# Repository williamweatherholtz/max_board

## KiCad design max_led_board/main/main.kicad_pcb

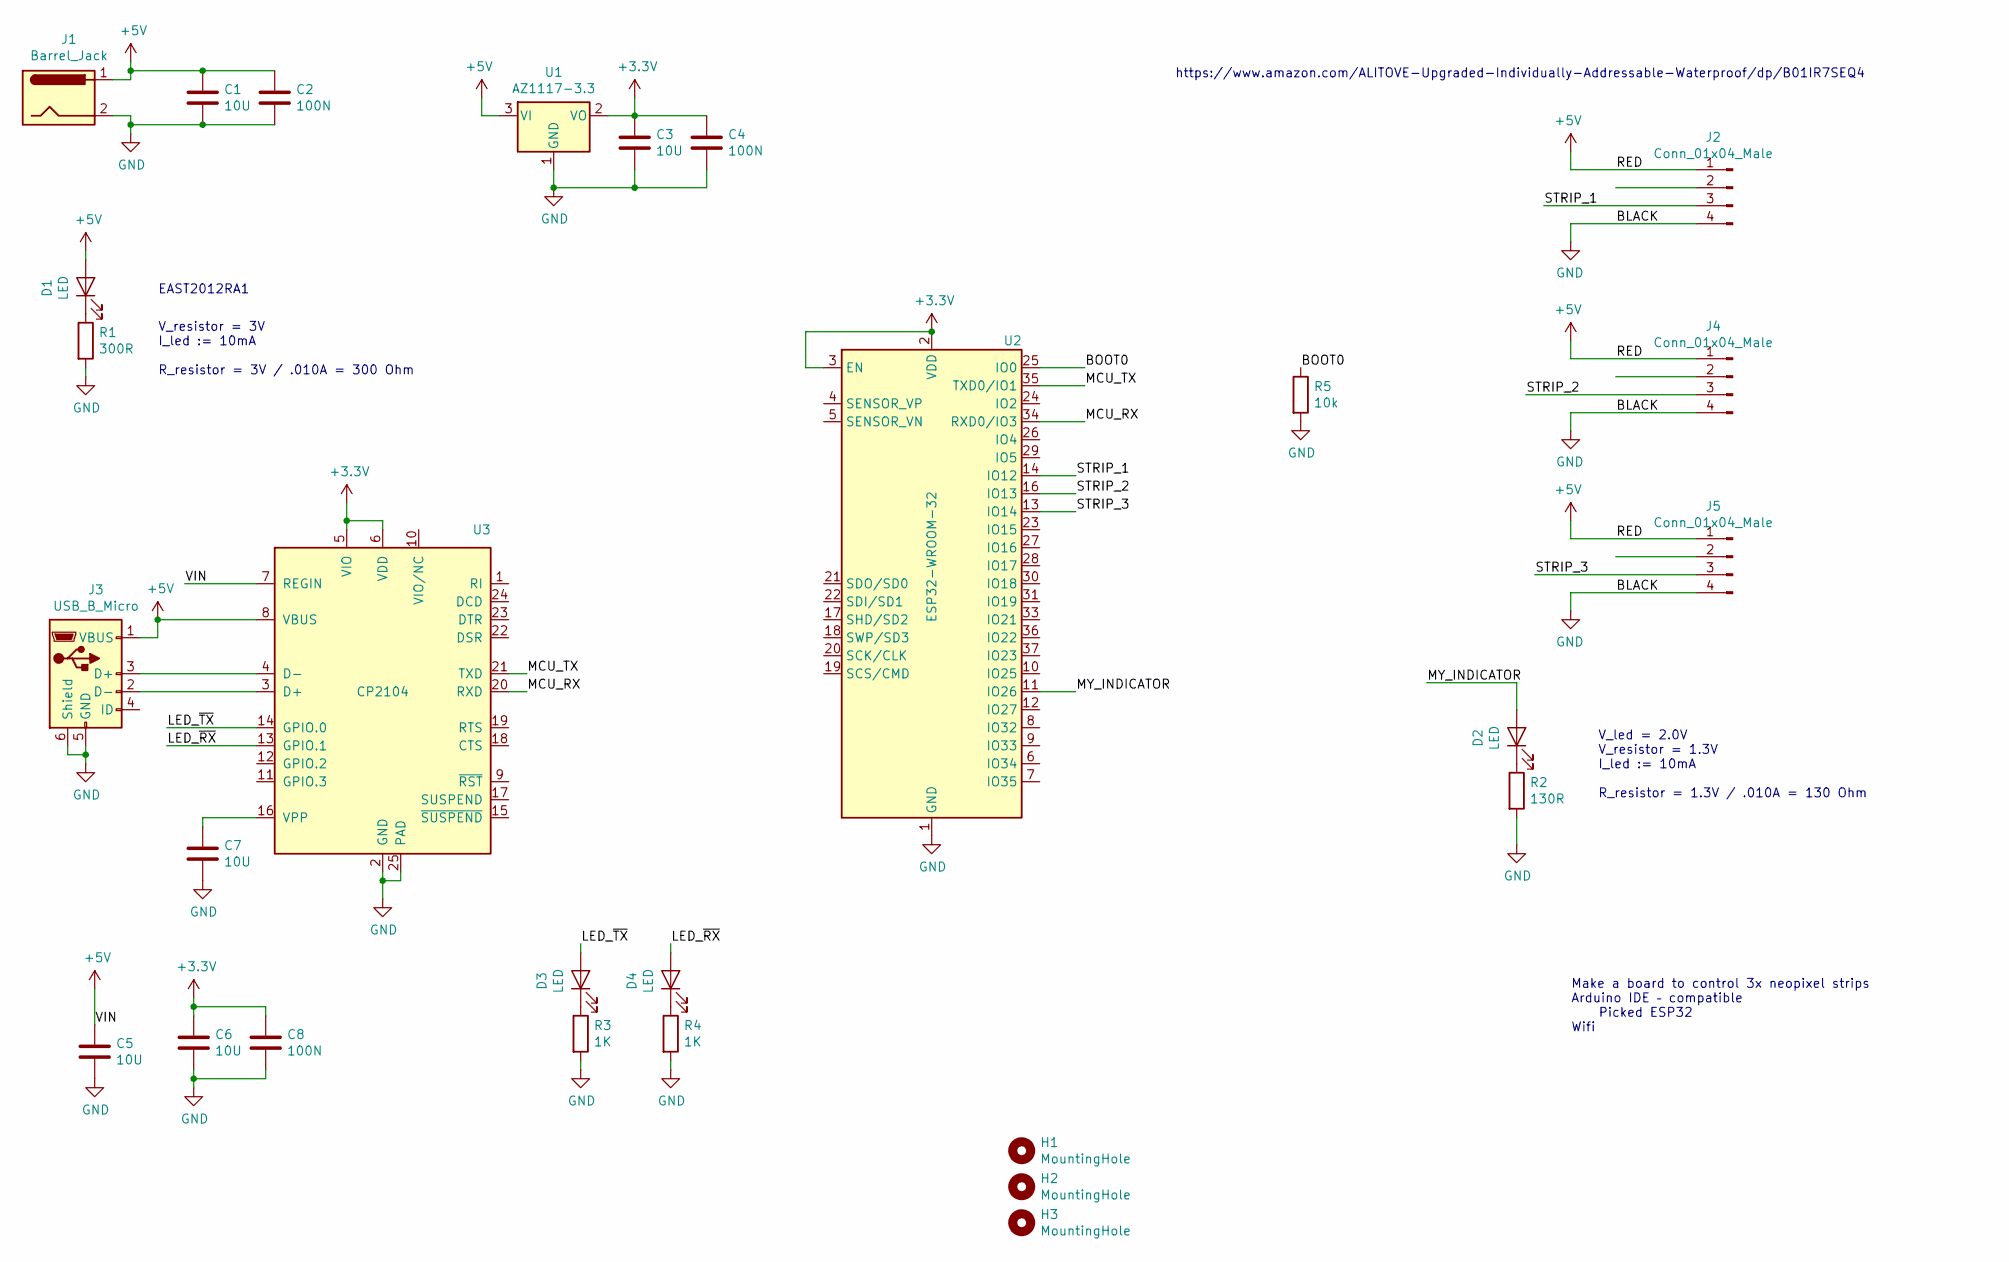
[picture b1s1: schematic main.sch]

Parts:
C1, C3, C5, C6, C7: 10U; C_0805_2012Metric
C2, C4, C8: 100N; C_0603_1608Metric
D1, D2, D3, D4: LED; LED_0805_2012Metric
H1, H2, H3: MountingHole; MountingHole_4.3mm_M4
J1: Barrel_Jack; BarrelJack_Wuerth_6941xx301002
J2, J4, J5: Conn_01x04_Male; PinHeader_1x04_P2.54mm_Vertical
J3: USB_B_Micro; USB_Micro_B_Female_10118194-0001LF
R1: 300R; R_0603_1608Metric
R2: 130R; R_0603_1608Metric
R3, R4: 1K; R_0603_1608Metric
R5: 10k; R_0603_1608Metric
U1: AZ1117-3.3; SOT-223-3_TabPin2
U2: ESP32-WROOM-32
U3: CP2104; QFN-24-1EP_4x4mm_P0.5mm_EP2.6x2.6mm

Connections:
+3V3: C3.1, C4.1, C6.1, C8.1, U1.2 (VO), U2.2 (VDD), U2.3 (EN), U3.5 (VIO), U3.6 (VDD)
+5V: C1.1, C2.1, C5.1, D1.2 (A), J1.1, J2.1, J3.1 (VBUS), J4.1, J5.1, U1.3 (VI), U3.7 (REGIN), U3.8 (VBUS)
/BOOT0: R5.1, U2.25 (IO0)
/LED_~RX~: D4.2 (A), U3.13 (GPIO.1)
/LED_~TX~: D3.2 (A), U3.14 (GPIO.0)
/MCU_RX: U2.34 (RXD0/IO3), U3.20 (RXD)
/MCU_TX: U2.35 (TXD0/IO1), U3.21 (TXD)
/MY_INDICATOR: D2.2 (A), U2.11 (IO26)
/STRIP_1: J2.3, U2.14 (IO12)
/STRIP_2: J4.3, U2.16 (IO13)
/STRIP_3: J5.3, U2.13 (IO14)
GND: C1.2, C2.2, C3.2, C4.2, C5.2, C6.2, C7.2, C8.2, J1.2, J2.4, J3.5 (GND), J3.6 (Shield), J4.4, J5.4, R1.2, R2.2, R3.2, R4.2, R5.2, U1.1 (GND), U2.1 (GND), U2.15 (GND), U2.38 (GND), U2.39 (GND), U3.2 (GND), U3.25 (PAD)
unnamed: C7.1, U3.16 (VPP)
unnamed: D1.1 (K), R1.1
unnamed: D2.1 (K), R2.1
unnamed: D3.1 (K), R3.1
unnamed: D4.1 (K), R4.1
unnamed: J3.2 (D-), U3.3 (D+)
unnamed: J3.3 (D+), U3.4 (D-)

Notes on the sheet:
Make a board to control 3x neopixel strips Arduino IDE – compatible Picked ESP32 Wifi
https://www.amazon.com/ALITOVE-Upgraded-Individually-Addressable-Waterproof/dp/B01IR7SEQ4
EAST2012RA1
V_resistor = 3V I_led := 10mA R_resistor = 3V / .010A = 300 Ohm
V_led = 2.0V V_resistor = 1.3V I_led := 10mA R_resistor = 1.3V / .010A = 130 Ohm

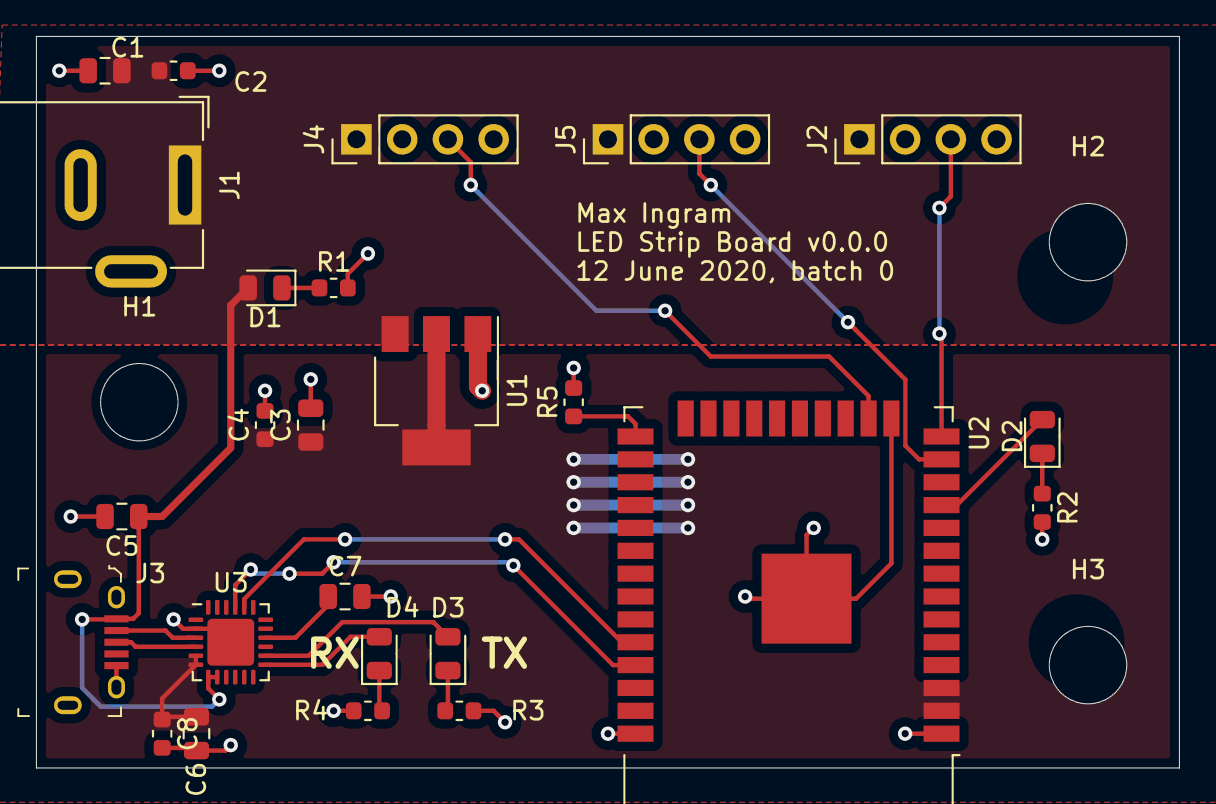
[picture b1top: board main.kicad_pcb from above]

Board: 2 copper layers, 63.5 x 40.6 mm, 28 parts (0 on the bottom side), 19 nets.

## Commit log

2020-06-11 init
2020-06-12 post class
